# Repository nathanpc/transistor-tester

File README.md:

# Transistor Tester

A really simple and useful transistor tester.

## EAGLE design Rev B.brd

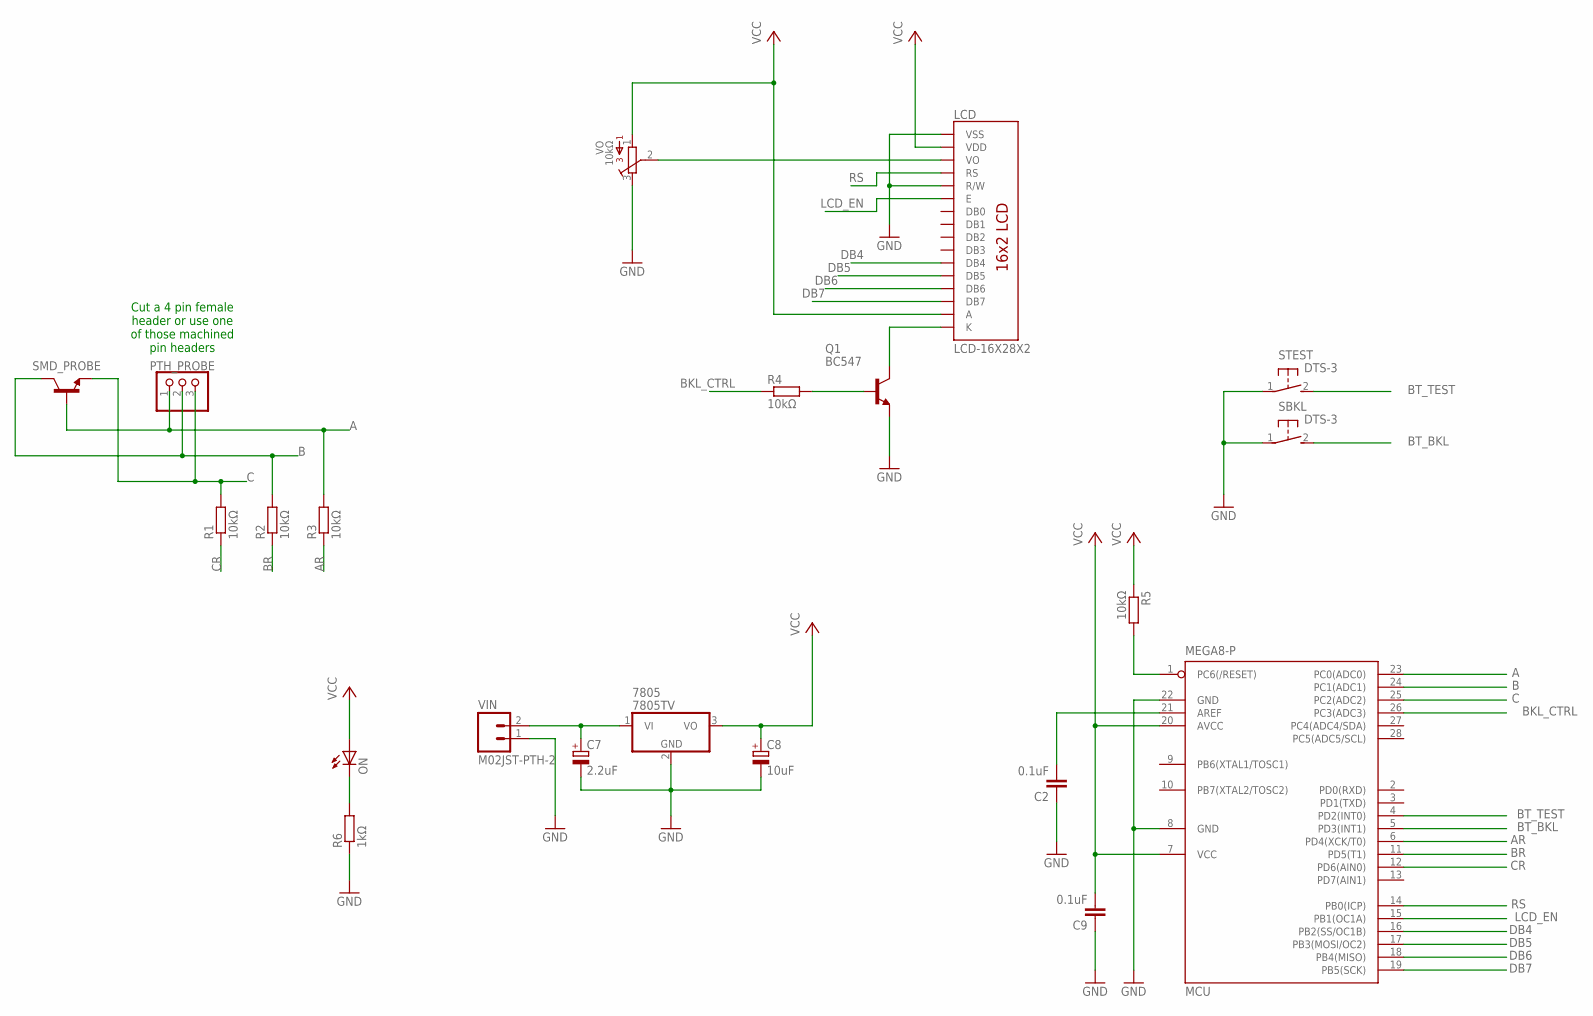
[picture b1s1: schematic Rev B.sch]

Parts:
7805: 7805TV; TO220V
C2: 0.1uF; C025-025X050
C7: 2.2uF; E2,5-6
C8: 10uF; E2,5-6
C9: 0.1uF; C050-025X075
LCD: LCD-16X28X2; LCD-8X2
MCU: MEGA8-P; DIL28-3
ON: LED3MM
PTH_PROBE: PINHD-1X3; 1X03
Q1: BC547; TO92
R1, R2, R3, R4, R5: 10kΩ; 0207/10
R6: 1kΩ; 0207/10
SBKL: DTS-3
SMD_PROBE: BC817-25SMD; SOT23-BEC
STEST: DTS-3
VIN: M02JST-PTH-2; JST-2-PTH
VO: 10kΩ; 3362H

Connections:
A: MCU.23 (PC0(ADC0)), PTH_PROBE.1, R3.2, SMD_PROBE.B
AR: MCU.6 (PD4(XCK/T0)), R3.1
B: MCU.24 (PC1(ADC1)), PTH_PROBE.2, R2.2, SMD_PROBE.C
BKL_CTRL: MCU.26 (PC3(ADC3)), R4.1
BR: MCU.11 (PD5(T1)), R2.1
BT_BKL: MCU.5 (PD3(INT1)), SBKL.2
BT_TEST: MCU.4 (PD2(INT0)), STEST.2
C: MCU.25 (PC2(ADC2)), PTH_PROBE.3, R1.2, SMD_PROBE.E
CR: MCU.12 (PD6(AIN0)), R1.1
DB4: LCD.11 (DB4), MCU.16 (PB2(SS/OC1B))
DB5: LCD.12 (DB5), MCU.17 (PB3(MOSI/OC2))
DB6: LCD.13 (DB6), MCU.18 (PB4(MISO))
DB7: LCD.14 (DB7), MCU.19 (PB5(SCK))
GND: 7805.2 (GND), C2.1, C7.-, C8.-, C9.1, LCD.1 (VSS), LCD.5 (R/W), MCU.8 (GND), MCU.22 (GND), Q1.1 (E), R6.1, SBKL.1, STEST.1, VIN.1, VO.3
LCD_EN: LCD.6 (E), MCU.15 (PB1(OC1A))
unnamed: C2.2, MCU.21 (AREF)
unnamed: LCD.16 (K), Q1.3 (C)
unnamed: Q1.2 (B), R4.2
unnamed: ON.K (C), R6.2
unnamed: 7805.1 (VI), C7.+, VIN.2
unnamed: LCD.3 (VO), VO.2
RESET: MCU.1 (PC6(/RESET)), R5.2
RS: LCD.4 (RS), MCU.14 (PB0(ICP))
VCC: 7805.3 (VO), C8.+, C9.2, LCD.2 (VDD), LCD.15 (A), MCU.7 (VCC), MCU.20 (AVCC), ON.A, R5.1, VO.1

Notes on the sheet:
Cut a 4 pin female header or use one of those machined pin headers

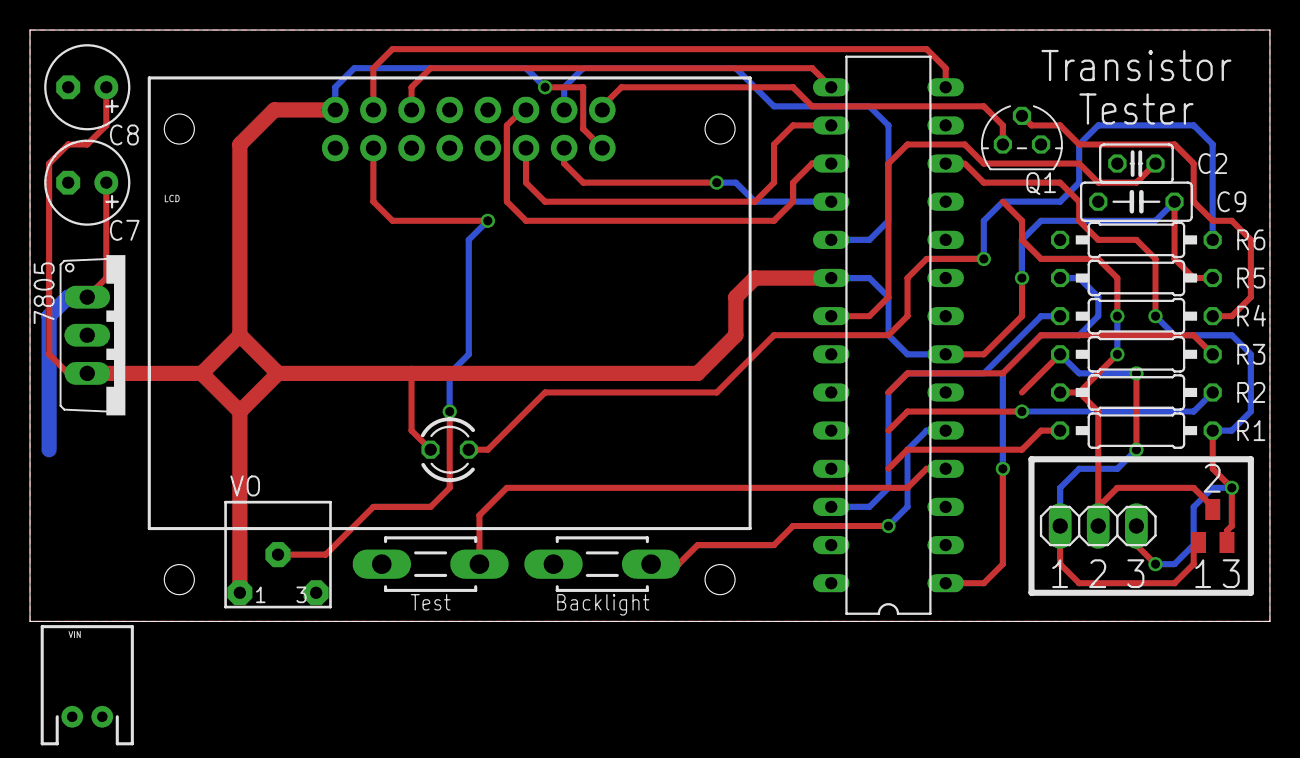
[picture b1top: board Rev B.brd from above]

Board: 2 copper layers, 82.5 x 39.4 mm, 21 parts (0 on the bottom side), 24 nets.

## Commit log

2013-06-23 First part of the schematic
2013-07-01 Did a lot of stuff in the firmware
2013-10-12 Switching from a MSP430 to a ATtiny2312
2013-10-12 Added a bunch of stuff
2013-10-12 Made a bunch of changes and started working in the board layout
2013-10-12 Started working on the board layout
2013-10-12 Time to start routing
2013-10-13 DONE
2013-10-25 Rev B schematic

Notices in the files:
parts and their libraries:
SparkFun-Displays: Licensing: CC v3.0 Share-Alike You are welcome to use this library for commercial purposes.
